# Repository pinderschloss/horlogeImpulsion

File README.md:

https://bit.ly/2SEGcSN
# horlogeImpulsion
Contrôleur d'horloge fille à impulsion, en subsitution à une horloge mère. Permet, selon les configurations, le pilotage par une boitier autonome alimenté par pile, batterie, ou port USB.
Il est conçu autour:
- d'un programme dont les options de compilation doivent être adaptées au besoin,
- et d'un circuit imprimé unique sur lequel l'implémentation des composant varie en fonction des besoins.

Convient (testé) pour:
- Brillié 'rosace 10 ohms' à impulsions électriques alternées (2 impulsions par minute) sur 2 piles AA, soit en pas simples toutes les 30secondes, soit en double pas toutes les minutes.
- Bodet '24V' à impulsions électriques alternées (1 impulsion par minute) sur alimentation USB.
- IBM '24V' à impulsions électriques non-alternées sur alimentation USB. 

Devrait convenir pour:
- Tout type d'horloge fille à impulsions alternée ou non, nécessitant une tension entre 2 et 36V, sur tout type d'alimentation entre 2 et 5V.

## Description :
Le controleur se base sur:
- une base de temps électronique (RTC : real time clock).
- une alimentation - n’importe quelle source délivrant entre 3V et 5V continu.
- un microcontroleur ATTinyx5 (25, 45 ou 85; testé uniquement sur Attiny85)

## Composants :
1.	Platine
2.	Microcontrôleur ATTINYx5-20PU (testé sur ATTINY85-20PU)
3.	Module RTC (la pile est facultative et ne sert pas) - testé sur un DS3231
4.	Boitier de pile ou alimentation microUSB
5.	Bouton poussoir de réglage
Selon les versions/besoin:
6.	Interrupteur ON/OFF 
7.	Pont en H et bornier pour relier la platine à l’horloge (avec sa résistance de 10 ohms)
8. transistor et bornier de sortie directe
9. bornier de sortie pour contrôle d'un pont H extérieur
10. Module convertisseur (élévateur) de tension vers la tension de fonctionnement de l'horloge (généralement 18V ou 24V)

## Brancher la platine à l’horloge :
### Brillié (10Ohms) 
-  Eteindre le contrôleur (interrupteur ON/OFF) ou bien débrancher l'alimentation
-  Relier bornes de sortie de la platine  avec les bornes d’entrée de l’horloge (2 fils). Laisser la résistance de 10ohm qui relie les deux bornes à vis .
-  Fixer l’ensemble des éléments au dos de l’horloge en assurant que l’on puisse manipuler : 
   -  les 2 interrupteurs (ON/OFF et le bouton poussoir AVANCE),
   -  le bouton,
   -  le boitier de piles.
-  Rallumer le contrôleur (interrupteur ON/OFF) ou bien brancher l'alimentation
-  Appuyer plusieurs secondes sur le bouton AVANCE, pour faire avancer l’aiguille des minutes de quelques minutes.
-  Quelques après avoir relâché le bouton AVANCE, regarder la position de l’aiguille des minutes :
   -  Si elle est alignée sur un point du cadran indiquant les minute, passer à l’étape de mise à l’heure.
   -  Sinon, elle se trouve au milieu entre deux points de minutes. Recommencer cette étape de branchement en inversant les deux fils qui relient la platine à l’horloge.

### Horloges à impulsions alternées
- Si la tension requise est supérieure à la tension d'alimentation, relier le pont en H externe (4 fils: VP, GND, S1 et S2) et brancher l'horloge comme une Brillié (10ohms) depuis le pont en H.
- Sinon (pas d'élévation de tension), procéder comme pour les Brillié (10ohms)

### Horloges à impulsions monopôlaires (pas d'inversion de polarité)
Ces horloges peuvent avoir 2 ou 3 fils. La platine peut elle-même comporter un bornier double ou triple. Toutes les combinaisons sont possibles. Attention: ne pas considérer ni connecter le fil de masse de l'horloge.
- S'il y a deux fils: en connecter un sur le connecteur marqué "rouge" (vers le coin de la platine) et l'autre fil dans l'autre bornier (n'importe lequel s'il y en a deux)
- S'il a 3 fils: le fil rouge doit être connecté à la platine sur le connecteur marqué "rouge" (vers le coin de la platine), et les deux autres soit ensemble soit séparemment dans le ou les les autres connecteurs du borniers.
- Lorsqu'on appuie sur le bouton poussoir AVANCE, vérifier que l'aiguille avance bien d'une minute.

## Mettre à l’heure l’horloge
-	Eteindre le contrôleur (interrupteur ON/OFF)
-	Approcher de l’heure réelle à la main, sans la dépasser (environ cinq à dix minutes avant l’heure réelle), en agissant directement sur le mécanisme. Pour cela agir directement sur le mécanisme d'entrainement (dépend du mécanisme - en général on peut l'avance et le reculer avec les deux mains ou tournevis), ou bien allumer le controleur et appuyer sur le bouton AVANCE sans le relacher (la vitesse d'avancement augmente lorsqu'on reste appuyé, mais cette opération peut être un peu fastidieuse).
-  Allumer le contrôleur (interrupteur ON/OFF)
-	En appuyant sur le bouton AVANCE, faire avancer jusqu’à afficher l’heure actuelle. A ce stade, l’horloge a de 0 à 59 secondes de retard.
-	Surveiller le nombre de secondes de l’heure réelle. Entre 55s et 59s, appuyer sur le bouton AVANCE. L’aiguille des minutes passe à la minute suivante: relacher immédiatement.

Note : 
-	 Ce réglage s’effectue de la même façon quel que soit le mode choisi (mode 60 : minute entière, ou mode 30 : demi minute), et se fait sur les minutes entières uniquement.
-	Compte tenu du temps variable de prise en compte de l’appui sur le bouton AVANCE, il est difficile d’obtenir une synchronisation meilleure que 2 secondes.

## Choix du mode de fonctionnement :
Identifier les caractéristiques de l'horloge:
- voltage
- nombre de fils
- type de 'moteur': 
  - électro-aimant et crabot sur roue crantée = impulsions non-alternées (les impulsion alternées fonctionneront aussi)
  - moteur type pendule et mécanisme d'échapement = impulsions alternées
  - moteur type Lavet (pas-à-pas 2 pas) = impulsions alternées
- période : temps minimal entre deux états stables de l'entrainement: 30 secondes ou 60 secondes. A tester à la main.

Attention: pour les horloges de période différentes de 30s ou 60s, il faudra modifier le programme (et pas seulement les options de compilation).

Pour les horloges dont la période est 30s:
- choisir si on souhaite un mouvement toutes les 30 secondes, ou un double mouvement toutes les 60s
- Ce choix n’a pas d’influence sur la précision de l’horloge. Le bruit produit par l’avancée de l’aiguille est différent selon le mode (un ‘clac’, ou bien un double ‘clac’ mais deux fois moins fréquent).

## Préparation de la platine
Voir le BOM.txt

## Programmation du microcontroleur :
- Le code est disponible à l’adresse suivante https://github.com/pinderschloss/horlogeImpulsion/
- Platine et code sont prévus pour fonctionner avec les microcontrôleurs ATTINYx5-20PU (x5 : 25 ou 45 ou 85) d’ATMEL. La consommation d'énergie est réduite autant que possible par une utilisation du mode sommeil autant de possible.
- La programmation du microcontrôleur peut se faire par une carte arduino par exemple (chercher Arduino ISP).
- Attention le microcontroleur ne peut pas être programmé en place sur le circuit imprimé.
- Le code est adaptable pour fonctionner avec des horloges nécessitant des signaux différents, en commentant ou décommentant les options de compilation.

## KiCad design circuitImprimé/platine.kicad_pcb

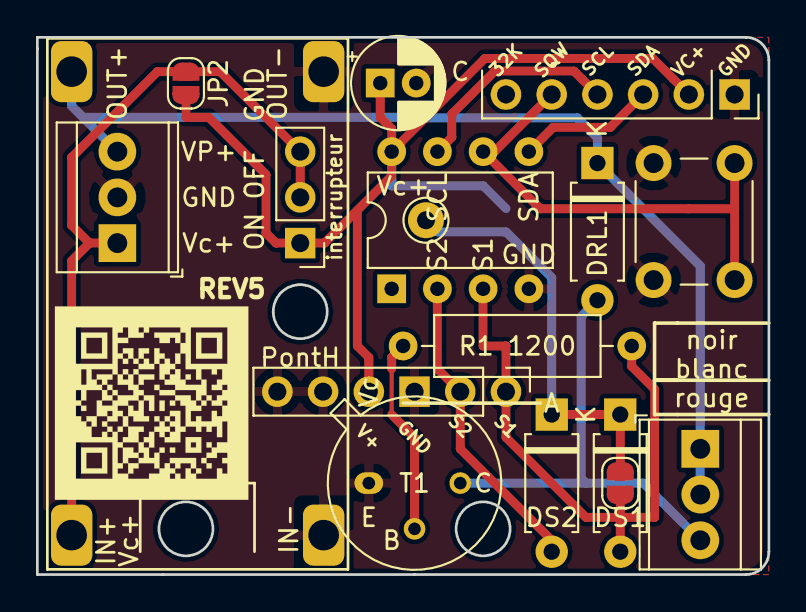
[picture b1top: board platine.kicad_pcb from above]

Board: 2 copper layers, 40.6 x 29.8 mm, 18 parts (1 on the bottom side), 12 nets.

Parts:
Alimentation1: bornier 3x2.54; TerminalBlock_TE_282834-3_1x03_P2.54mm_Horizontal
C: condensateur; CP_Radial_D5.0mm_P2.00mm
DRL1: Roue libre; D_A-405_P7.62mm_Horizontal
DS1, DS2: DIODE; D_A-405_P7.62mm_Horizontal
JP2: alim_controle_permanente; SolderJumper-2_P1.3mm_Open_RoundedPad1.0x1.5mm
JPS1: monoP; SolderJumper-2_P1.3mm_Open_RoundedPad1.0x1.5mm
Microcontroleur1: ATtiny85-20PU; DIP-8_W7.62mm
PontH: Fiches2.54; connecteurPontH
R1 1200: Ibase T1; R_Axial_DIN0309_L9.0mm_D3.2mm_P12.70mm_Horizontal
RTC: fiches2.54; RTCDS321surPINHEADER
Reglage: Inter-pousser; SW_PUSH_6mm_H4.3mm
SW1: Inter-controle; PinHeader_1x03_P2.54mm_Vertical
T1: NPN; TO-39-3_Window
U1: USB-x-tension; USB-x-tension-module
monopolaire: bornier 3x2.54; TerminalBlock_TE_282834-3_1x03_P2.54mm_Horizontal
x-tension ENABLE: enable-x-tension; Pin_D1.0mm_L10.0mm
x-tension-permanent: x-tension-permanent; SolderJumper-2_P1.3mm_Open_RoundedPad1.0x1.5mm

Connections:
/Reveil: Microcontroleur1.6, RTC.5, Reglage.1
/SCL-INT0: Microcontroleur1.7, RTC.4
/SDA: Microcontroleur1.5, RTC.3
/VP+: Alimentation1.3, DRL1.1, U1.3, monopolaire.1, monopolaire.2
/Vc+: C.1, JP2.2, Microcontroleur1.8, PontH.4, RTC.2, SW1.1, x-tension-permanent.2
GND: Alimentation1.2, C.2, Microcontroleur1.4, PontH.3, PontH.5, PontH.6, RTC.1, Reglage.2, T1.1, U1.2
unnamed: Alimentation1.1, JP2.1, SW1.2, SW1.3, U1.1
unnamed: DRL1.2, T1.3, monopolaire.3
unnamed: DS1.1, DS2.1, JPS1.1, x-tension ENABLE.1, x-tension-permanent.1
unnamed: R1 1200.1, T1.2
S1: DS1.2, JPS1.2, Microcontroleur1.3, PontH.1, R1 1200.2
S2: DS2.2, Microcontroleur1.2, PontH.2

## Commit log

2018-03-19 Rajout des photos d'illustration (PHOTOS) Création du répertoire PLATINE Correction de la BOM (erreurs de frappe)
2019-03-29 Rename BOM.txt to BOM.md
2019-03-29 essai
2019-03-29 ajout images et instructions montage
2019-03-30 Explications sur la préparation des modules, mise à jour programme
2019-03-30 ajout images et instructions montage
    Explications sur la préparation des modules, mise à jour programme
2019-03-30 mise à jour mineure description
2019-03-30 ajout images et instructions montage
    Explications sur la préparation des modules, mise à jour programme
    Explications sur la préparation des modules, mise à jour programme
    mise à jour mineure description
2019-03-30 correction nom fichier sketch arduino
2019-03-30 raz fichier préparation module
2019-03-30 correction nom fichier sketch arduino
    raz fichier préparation module
2019-03-30 fusion de modifications mineures
    raz fichier préparation module
    correction nom fichier sketch arduino
    raz fichier préparation module
2019-03-30 Première version fonctionnelle.
2019-03-30 Description horloges électriques Brillié 10ohms
2019-03-30 corrections typo
2019-03-30 ajout des descriptions partielles de IBM, SIMPLEX, BODET
2019-03-30 ajout du lien vers Aisler
